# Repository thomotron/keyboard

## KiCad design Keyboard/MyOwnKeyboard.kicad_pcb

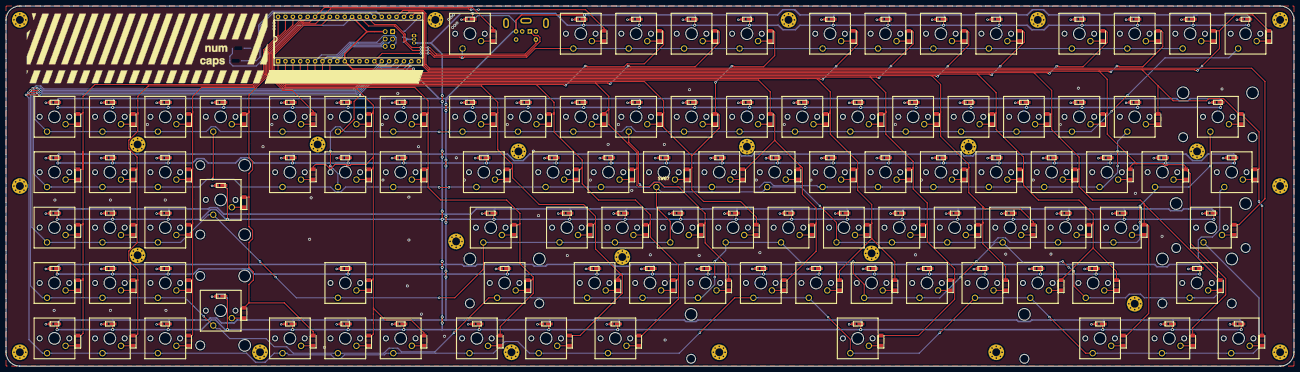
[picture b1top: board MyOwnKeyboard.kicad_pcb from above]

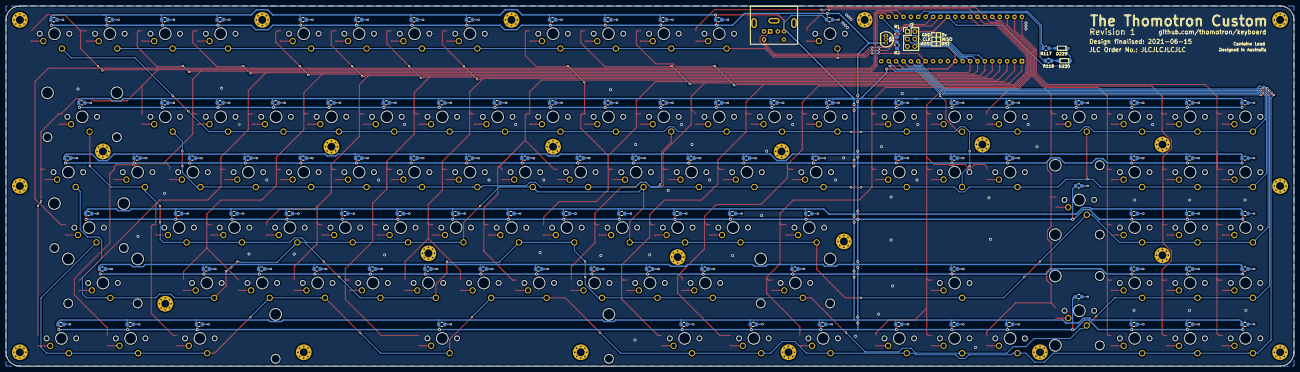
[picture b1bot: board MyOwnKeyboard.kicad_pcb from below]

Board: 2 copper layers, 441.8 x 123.5 mm, 438 parts (110 on the bottom side), 239 nets.

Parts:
D5, D6, D7, D8, D9, D10, D12, D13, D14, D15, D16, D17, D18, D20, D21, D22, D23, D24, D25, D26, D27, D28, D29, D30, D31, D32, D33, D34, D35, D36, D37, D39, D40, D41, D42, D43, D44, D45, D46, D47, D48, D49, D50, D51, D52, D53, D54, D55, D56, D58, D59, D60, D61, D62, D63, D64, D65, D66, D67, D68, D69, D70, D71, D72, D73, D74, D75, D77, D78, D79, D80, D81, D82, D83, D84, D85, D86, D87, D88, D89, D90, D91, D92, D94, D96, D97, D98, D99, D100, D101, D102, D103, D106, D107, D108, D109, D110, D111, D112, D113, D114: 1N4148; D_MiniMELF
D119, D120, D121, D122, D123, D124, D126, D127, D128, D129, D130, D131, D132, D134, D135, D136, D137, D138, D139, D140, D141, D142, D143, D144, D145, D146, D147, D148, D149, D150, D151, D153, D154, D155, D156, D157, D158, D159, D160, D161, D162, D163, D164, D165, D166, D167, D168, D169, D170, D172, D173, D174, D175, D176, D177, D178, D179, D180, D181, D182, D183, D184, D185, D186, D187, D188, D189, D191, D192, D193, D194, D195, D196, D197, D198, D199, D200, D201, D202, D203, D204, D205, D206, D208, D210, D211, D212, D213, D214, D215, D216, D217, D220, D221, D222, D223, D224, D225, D226, D227, D228: LED; 158301250
D229: NUMLOCK; 158301250_Face_Down
D230: CAPSLOCK; 158301250_Face_Down
J1: Mini-DIN-6; Connector_Mini-DIN_Female_6Pin_2rows
J2: ISP Header; PinHeader_2x03_P2.54mm_Vertical
M1, M2, M3, M4, M5, M6, M7, M8, M9, M10, M11, M12, M13, M14, M15, M16, M17, M18, M19, M20, M21, M22, M23, M24: MountingHole_2.7mm_M2.5_Pad_Via
Q1: 2N7000; TO-92_Inline
R1: 100; R_0805_2012Metric_Pad1.15x1.40mm_HandSolder
R2: 100k; R_0805_2012Metric_Pad1.15x1.40mm_HandSolder
R7, R8, R9, R10, R11, R12, R14, R15, R16, R17, R18, R19, R20, R22, R23, R24, R25, R26, R27, R28, R29, R30, R31, R32, R33, R34, R35, R36, R37, R38, R39, R41, R42, R43, R44, R45, R46, R47, R48, R49, R50, R51, R52, R53, R54, R55, R56, R57, R58, R60, R61, R62, R63, R64, R65, R66, R67, R68, R69, R70, R71, R72, R73, R74, R75, R76, R77, R79, R80, R81, R82, R83, R84, R85, R86, R87, R88, R89, R90, R91, R92, R93, R94, R96, R98, R99, R100, R101, R102, R103, R104, R105, R108, R109, R110, R111, R112, R113, R114, R115, R116, R117, R118: 2.26k; R_0805_2012Metric_Pad1.15x1.40mm_HandSolder
SW5, SW6, SW7, SW8, SW9, SW10, SW12, SW13, SW14, SW15, SW16, SW17, SW18, SW20, SW21, SW22, SW23, SW24, SW25, SW26, SW27, SW28, SW29, SW30, SW31, SW32, SW33, SW34, SW35, SW36, SW37, SW39, SW40, SW41, SW42, SW43, SW44, SW46, SW47, SW48, SW49, SW50, SW51, SW52, SW53, SW54, SW55, SW56, SW58, SW59, SW60, SW62, SW64, SW65, SW66, SW67, SW68, SW69, SW70, SW71, SW72, SW73, SW74, SW77, SW78, SW79, SW81, SW83, SW84, SW85, SW86, SW87, SW88, SW89, SW90, SW91, SW96, SW97, SW98, SW99, SW100, SW106, SW107, SW109, SW110: SW_SPST; SW_Cherry_MX_1.00u_PCB
SW45, SW94: SW_SPST; SW_Cherry_MX_1.50u_PCB
SW61, SW80: SW_SPST; SW_Cherry_MX_2.00u_Vertical_PCB
SW63: SW_SPST; SW_Cherry_MX_1.75u_PCB
SW75: SW_SPST; SW_Cherry_MX_2.00u_PCB
SW82, SW114: SW_SPST; SW_Cherry_MX_2.25u_PCB
SW92: SW_SPST; SW_Cherry_MX_2.75u_PCB
SW101, SW102, SW103, SW111, SW112, SW113: SW_SPST; SW_Cherry_MX_1.25u_PCB
SW108: SW_SPST; SW_Cherry_MX_7.00u_PCB
U1: ATmega8535-16PU; DIP-40_W15.24mm_Socket

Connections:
1: SW5.1, SW6.1, SW7.1, SW8.1, SW9.1, SW10.1, SW12.1, SW13.1, SW14.1, SW15.1, SW16.1, SW17.1, SW18.1, U1.14
2: SW20.1, SW21.1, SW22.1, SW23.1, SW24.1, SW25.1, SW26.1, SW27.1, SW28.1, SW29.1, SW30.1, SW31.1, SW32.1, SW33.1, SW34.1, SW35.1, SW36.1, SW37.1, U1.15
3: SW39.1, SW40.1, SW41.1, SW42.1, SW43.1, SW44.1, SW45.1, SW46.1, SW47.1, SW48.1, SW49.1, SW50.1, SW51.1, SW52.1, SW53.1, SW54.1, SW55.1, SW56.1, U1.16
4: SW58.1, SW59.1, SW60.1, SW61.1, SW62.1, SW63.1, SW64.1, SW65.1, SW66.1, SW67.1, SW68.1, SW69.1, SW70.1, SW71.1, SW72.1, SW73.1, SW74.1, SW75.1, U1.17
5: SW77.1, SW78.1, SW79.1, SW80.1, SW81.1, SW82.1, SW83.1, SW84.1, SW85.1, SW86.1, SW87.1, SW88.1, SW89.1, SW90.1, SW91.1, SW92.1, SW94.1, U1.18
5v: D229.2, D230.2, J1.4, J2.2, R7.1, R8.1, R9.1, R10.1, R11.1, R12.1, R14.1, R15.1, R16.1, R17.1, R18.1, R19.1, R20.1, R22.1, R23.1, R24.1, R25.1, R26.1, R27.1, R28.1, R29.1, R30.1, R31.1, R32.1, R33.1, R34.1, R35.1, R36.1, R37.1, R38.1, R39.1, R41.1, R42.1, R43.1, R44.1, R45.1, R46.1, R47.1, R48.1, R49.1, R50.1, R51.1, R52.1, R53.1, R54.1, R55.1, R56.1, R57.1, R58.1, R60.1, R61.1, R62.1, R63.1, R64.1, R65.1, R66.1, R67.1, R68.1, R69.1, R70.1, R71.1, R72.1, R73.1, R74.1, R75.1, R76.1, R77.1, R79.1, R80.1, R81.1, R82.1, R83.1, R84.1, R85.1, R86.1, R87.1, R88.1, R89.1, R90.1, R91.1, R92.1, R93.1, R94.1, R96.1, R98.1, R99.1, R100.1, R101.1, R102.1, R103.1, R104.1, R105.1, R108.1, R109.1, R110.1, R111.1, R112.1, R113.1, R114.1, R115.1, R116.1, U1.10, U1.30
6: SW96.1, SW97.1, SW98.1, SW99.1, SW100.1, SW101.1, SW102.1, SW103.1, SW106.1, SW107.1, SW108.1, SW109.1, SW110.1, SW111.1, SW112.1, SW113.1, SW114.1, U1.19
/Clk: J1.5, U1.28
/Counter2A-PWM: R1.1, U1.21
/Data: J1.1, U1.29
A: D20.2, D39.2, D58.2, D77.2, D96.2, U1.40
B: D21.2, D40.2, D59.2, D78.2, D97.2, U1.39
C: D22.2, D41.2, D60.2, D79.2, D98.2, U1.38
D: D23.2, D42.2, D61.2, D80.2, D99.2, U1.37
E: D5.2, D24.2, D43.2, D62.2, D81.2, D100.2, U1.36
Earth: J1.3, J2.1, Q1.1, R2.2, U1.11, U1.25, U1.31
F: D6.2, D25.2, D44.2, D63.2, D82.2, D101.2, U1.35
G: D7.2, D26.2, D45.2, D64.2, D83.2, D102.2, U1.34
H: D8.2, D27.2, D46.2, D65.2, D84.2, D103.2, U1.33
I: D9.2, D28.2, D47.2, D66.2, D85.2, U1.1
J: D10.2, D29.2, D48.2, D67.2, D86.2, U1.2
K: D30.2, D49.2, D68.2, D87.2, D106.2, U1.3
L: D12.2, D31.2, D50.2, D69.2, D88.2, D107.2, U1.4
M: D13.2, D32.2, D51.2, D70.2, D89.2, D108.2, U1.5
MISO: D15.2, D34.2, D53.2, D72.2, D91.2, D110.2, J2.4, U1.7
MOSI: D14.2, D33.2, D52.2, D71.2, D90.2, D109.2, J2.5, U1.6
unnamed: D5.1, SW5.2
unnamed: D6.1, SW6.2
unnamed: D7.1, SW7.2
unnamed: D8.1, SW8.2
unnamed: D9.1, SW9.2
unnamed: D10.1, SW10.2
unnamed: D12.1, SW12.2
unnamed: D13.1, SW13.2
unnamed: D14.1, SW14.2
unnamed: D15.1, SW15.2
unnamed: D16.1, SW16.2
unnamed: D17.1, SW17.2
unnamed: D18.1, SW18.2
unnamed: D20.1, SW20.2
unnamed: D21.1, SW21.2
unnamed: D22.1, SW22.2
unnamed: D23.1, SW23.2
unnamed: D24.1, SW24.2
unnamed: D25.1, SW25.2
unnamed: D26.1, SW26.2
unnamed: D27.1, SW27.2
unnamed: D28.1, SW28.2
unnamed: D29.1, SW29.2
unnamed: D30.1, SW30.2
unnamed: D31.1, SW31.2
unnamed: D32.1, SW32.2
unnamed: D33.1, SW33.2
unnamed: D34.1, SW34.2
unnamed: D35.1, SW35.2
unnamed: D36.1, SW36.2
unnamed: D37.1, SW37.2
unnamed: D39.1, SW39.2
unnamed: D40.1, SW40.2
unnamed: D41.1, SW41.2
unnamed: D42.1, SW42.2
unnamed: D43.1, SW43.2
unnamed: D44.1, SW44.2
unnamed: D45.1, SW45.2
unnamed: D46.1, SW46.2
unnamed: D47.1, SW47.2
unnamed: D48.1, SW48.2
unnamed: D49.1, SW49.2
unnamed: D50.1, SW50.2
unnamed: D51.1, SW51.2
unnamed: D52.1, SW52.2
unnamed: D53.1, SW53.2
unnamed: D54.1, SW54.2
unnamed: D55.1, SW55.2
unnamed: D56.1, SW56.2
unnamed: D58.1, SW58.2
unnamed: D59.1, SW59.2
unnamed: D60.1, SW60.2
unnamed: D61.1, SW61.2
unnamed: D62.1, SW62.2
unnamed: D63.1, SW63.2
unnamed: D64.1, SW64.2
unnamed: D65.1, SW65.2
unnamed: D66.1, SW66.2
unnamed: D67.1, SW67.2
unnamed: D68.1, SW68.2
unnamed: D69.1, SW69.2
unnamed: D70.1, SW70.2
unnamed: D71.1, SW71.2
unnamed: D72.1, SW72.2
unnamed: D73.1, SW73.2
unnamed: D74.1, SW74.2
unnamed: D75.1, SW75.2
unnamed: D77.1, SW77.2
unnamed: D78.1, SW78.2
unnamed: D79.1, SW79.2
unnamed: D80.1, SW80.2
unnamed: D81.1, SW81.2
unnamed: D82.1, SW82.2
unnamed: D83.1, SW83.2
unnamed: D84.1, SW84.2
unnamed: D85.1, SW85.2
unnamed: D86.1, SW86.2
unnamed: D87.1, SW87.2
unnamed: D88.1, SW88.2
unnamed: D89.1, SW89.2
unnamed: D90.1, SW90.2
unnamed: D91.1, SW91.2
unnamed: D92.1, SW92.2
unnamed: D94.1, SW94.2
unnamed: D96.1, SW96.2
unnamed: D97.1, SW97.2
unnamed: D98.1, SW98.2
unnamed: D99.1, SW99.2
unnamed: D100.1, SW100.2
unnamed: D101.1, SW101.2
unnamed: D102.1, SW102.2
unnamed: D103.1, SW103.2
unnamed: D106.1, SW106.2
unnamed: D107.1, SW107.2
unnamed: D108.1, SW108.2
unnamed: D109.1, SW109.2
unnamed: D110.1, SW110.2
unnamed: D111.1, SW111.2
unnamed: D112.1, SW112.2
unnamed: D113.1, SW113.2
unnamed: D114.1, SW114.2
unnamed: D119.1, D120.1, D121.1, D122.1, D123.1, D124.1, D126.1, D127.1, D128.1, D129.1, D130.1, D131.1, D132.1, D134.1, D135.1, D136.1, D137.1, D138.1, D139.1, D140.1, D141.1, D142.1, D143.1, D144.1, D145.1, D146.1, D147.1, D148.1, D149.1, D150.1, D151.1, D153.1, D154.1, D155.1, D156.1, D157.1, D158.1, D159.1, D160.1, D161.1, D162.1, D163.1, D164.1, D165.1, D166.1, D167.1, D168.1, D169.1, D170.1, D172.1, D173.1, D174.1, D175.1, D176.1, D177.1, D178.1, D179.1, D180.1, D181.1, D182.1, D183.1, D184.1, D185.1, D186.1, D187.1, D188.1, D189.1, D191.1, D192.1, D193.1, D194.1, D195.1, D196.1, D197.1, D198.1, D199.1, D200.1, D201.1, D202.1, D203.1, D204.1, D205.1, D206.1, D208.1, D210.1, D211.1, D212.1, D213.1, D214.1, D215.1, D216.1, D217.1, D220.1, D221.1, D222.1, D223.1, D224.1, D225.1, D226.1, D227.1, D228.1, Q1.3
unnamed: D119.2, R7.2
unnamed: D120.2, R8.2
unnamed: D121.2, R9.2
unnamed: D122.2, R10.2
unnamed: D123.2, R11.2
unnamed: D124.2, R12.2
unnamed: D126.2, R14.2
unnamed: D127.2, R15.2
unnamed: D128.2, R16.2
unnamed: D129.2, R17.2
unnamed: D130.2, R18.2
unnamed: D131.2, R19.2
unnamed: D132.2, R20.2
unnamed: D134.2, R22.2
unnamed: D135.2, R23.2
unnamed: D136.2, R24.2
unnamed: D137.2, R25.2
unnamed: D138.2, R26.2
unnamed: D139.2, R27.2
unnamed: D140.2, R28.2
unnamed: D141.2, R29.2
unnamed: D142.2, R30.2
unnamed: D143.2, R31.2
unnamed: D144.2, R32.2
unnamed: D145.2, R33.2
unnamed: D146.2, R34.2
unnamed: D147.2, R35.2
unnamed: D148.2, R36.2
unnamed: D149.2, R37.2
unnamed: D150.2, R38.2
unnamed: D151.2, R39.2
unnamed: D153.2, R41.2
unnamed: D154.2, R42.2
unnamed: D155.2, R43.2
unnamed: D156.2, R44.2
unnamed: D157.2, R45.2
unnamed: D158.2, R46.2
unnamed: D159.2, R47.2
unnamed: D160.2, R48.2
unnamed: D161.2, R49.2
unnamed: D162.2, R50.2
unnamed: D163.2, R51.2
unnamed: D164.2, R52.2
unnamed: D165.2, R53.2
unnamed: D166.2, R54.2
unnamed: D167.2, R55.2
unnamed: D168.2, R56.2
unnamed: D169.2, R57.2
unnamed: D170.2, R58.2
unnamed: D172.2, R60.2
unnamed: D173.2, R61.2
unnamed: D174.2, R62.2
unnamed: D175.2, R63.2
unnamed: D176.2, R64.2
unnamed: D177.2, R65.2
unnamed: D178.2, R66.2
unnamed: D179.2, R67.2
unnamed: D180.2, R68.2
unnamed: D181.2, R69.2
unnamed: D182.2, R70.2
unnamed: D183.2, R71.2
unnamed: D184.2, R72.2
unnamed: D185.2, R73.2
unnamed: D186.2, R74.2
unnamed: D187.2, R75.2
unnamed: D188.2, R76.2
unnamed: D189.2, R77.2
unnamed: D191.2, R79.2
unnamed: D192.2, R80.2
unnamed: D193.2, R81.2
unnamed: D194.2, R82.2
unnamed: D195.2, R83.2
unnamed: D196.2, R84.2
unnamed: D197.2, R85.2
unnamed: D198.2, R86.2
unnamed: D199.2, R87.2
unnamed: D200.2, R88.2
unnamed: D201.2, R89.2
unnamed: D202.2, R90.2
unnamed: D203.2, R91.2
unnamed: D204.2, R92.2
unnamed: D205.2, R93.2
unnamed: D206.2, R94.2
unnamed: D208.2, R96.2
unnamed: D210.2, R98.2
unnamed: D211.2, R99.2
unnamed: D212.2, R100.2
unnamed: D213.2, R101.2
unnamed: D214.2, R102.2
unnamed: D215.2, R103.2
unnamed: D216.2, R104.2
unnamed: D217.2, R105.2
unnamed: D220.2, R108.2
unnamed: D221.2, R109.2
unnamed: D222.2, R110.2
unnamed: D223.2, R111.2
unnamed: D224.2, R112.2
unnamed: D225.2, R113.2
unnamed: D226.2, R114.2
unnamed: D227.2, R115.2
unnamed: D228.2, R116.2
unnamed: D229.1, R117.2
unnamed: D230.1, R118.2
unnamed: Q1.2, R1.2, R2.1
unnamed: R117.1, U1.26
unnamed: R118.1, U1.27
P: D16.2, D35.2, D54.2, D73.2, D92.2, D111.2, J2.3, U1.8
Q: D17.2, D36.2, D55.2, D74.2, D112.2, U1.22
R: D18.2, D37.2, D56.2, D75.2, D94.2, D113.2, U1.23
RESET: J2.6, U1.9
S: D114.2, U1.24

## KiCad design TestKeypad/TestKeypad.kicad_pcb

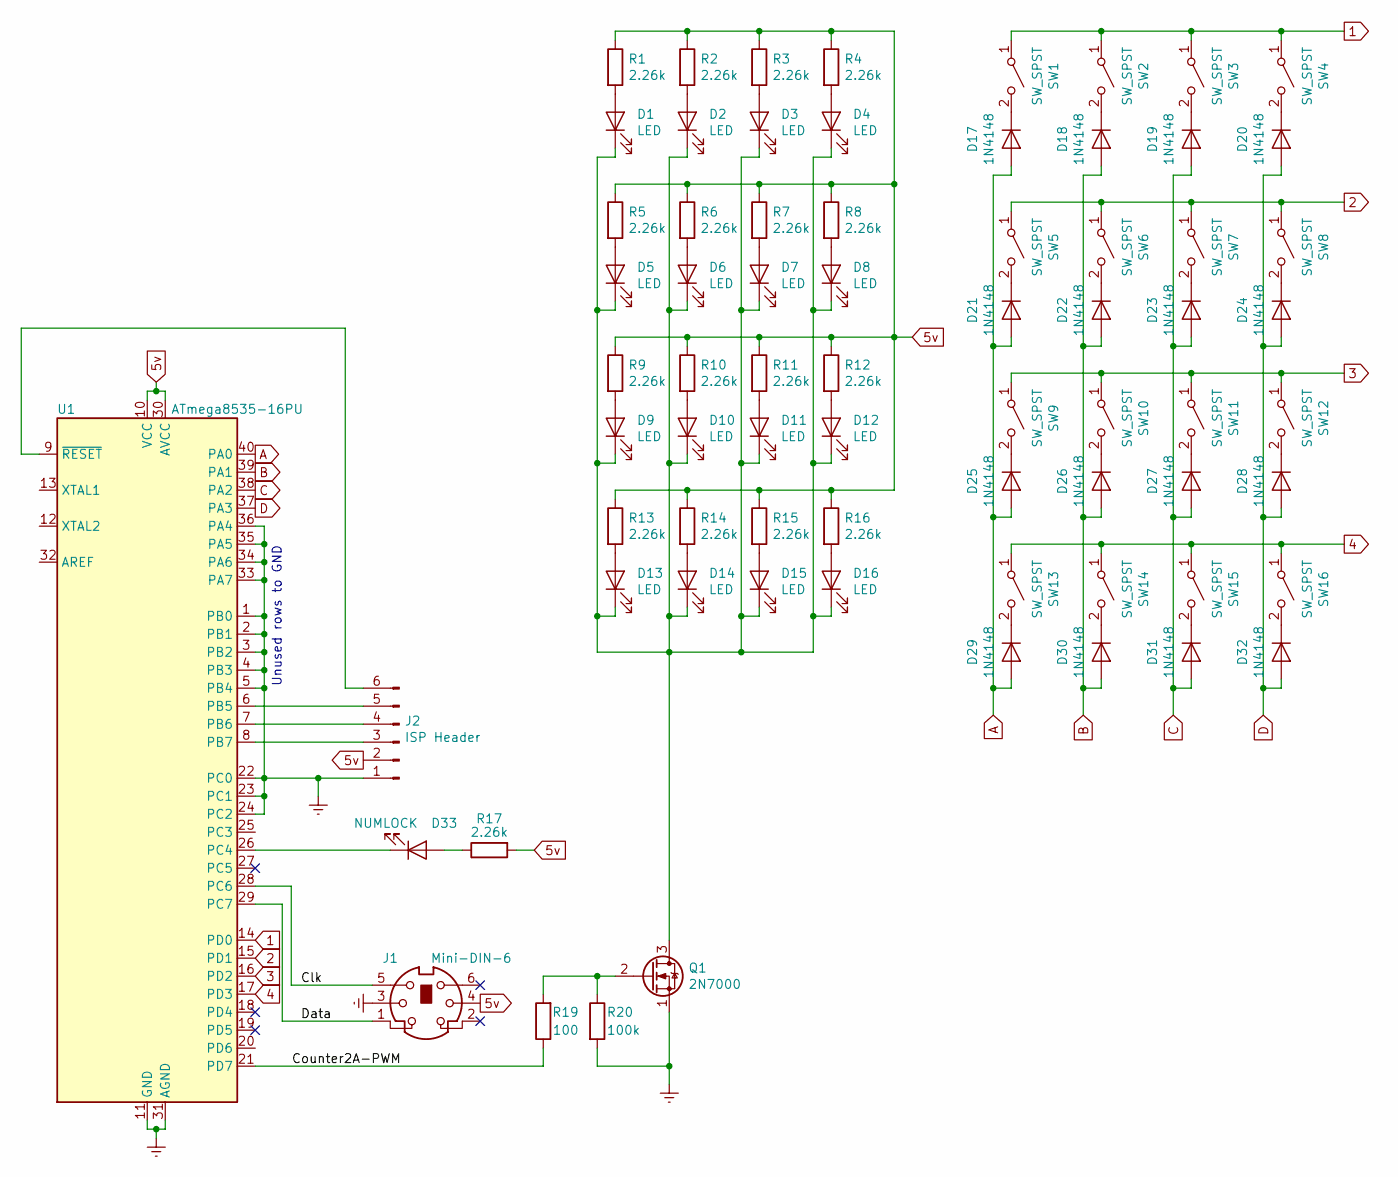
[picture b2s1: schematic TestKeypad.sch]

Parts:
D1, D2, D3, D4, D5, D6, D7, D8, D9, D10, D11, D12, D13, D14, D15, D16: LED; 158301250
D17, D18, D19, D20, D21, D22, D23, D24, D25, D26, D27, D28, D29, D30, D31, D32: 1N4148; D_MiniMELF
D33: NUMLOCK; 158301250
J1: Mini-DIN-6; Connector_Mini-DIN_Female_6Pin_2rows
J2: ISP Header; PinHeader_2x03_P2.54mm_Vertical
Q1: 2N7000; TO-92_Inline
R1, R2, R3, R4, R5, R6, R7, R8, R9, R10, R11, R12, R13, R14, R15, R16, R17: 2.26k; R_0805_2012Metric_Pad1.15x1.40mm_HandSolder
R19: 100; R_0805_2012Metric_Pad1.15x1.40mm_HandSolder
R20: 100k; R_0805_2012Metric_Pad1.15x1.40mm_HandSolder
SW1, SW2, SW3, SW4, SW5, SW6, SW7, SW8, SW9, SW10, SW11, SW12, SW13, SW14, SW15, SW16: SW_SPST; SW_Cherry_MX_1.00u_PCB
U1: ATmega8535-16PU; DIP-40_W15.24mm_Socket

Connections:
1: SW1.1 (A), SW2.1 (A), SW3.1 (A), SW4.1 (A), U1.14 (PD0)
2: SW5.1 (A), SW6.1 (A), SW7.1 (A), SW8.1 (A), U1.15 (PD1)
3: SW9.1 (A), SW10.1 (A), SW11.1 (A), SW12.1 (A), U1.16 (PD2)
4: SW13.1 (A), SW14.1 (A), SW15.1 (A), SW16.1 (A), U1.17 (PD3)
5v: J1.4, J2.2, R1.1, R2.1, R3.1, R4.1, R5.1, R6.1, R7.1, R8.1, R9.1, R10.1, R11.1, R12.1, R13.1, R14.1, R15.1, R16.1, R17.2, U1.10 (VCC), U1.30 (AVCC)
/Clk: J1.5, U1.28 (PC6)
/Counter2A-PWM: R19.1, U1.21 (PD7)
/Data: J1.1, U1.29 (PC7)
A: D17.2 (A), D21.2 (A), D25.2 (A), D29.2 (A), U1.40 (PA0)
B: D18.2 (A), D22.2 (A), D26.2 (A), D30.2 (A), U1.39 (PA1)
C: D19.2 (A), D23.2 (A), D27.2 (A), D31.2 (A), U1.38 (PA2)
D: D20.2 (A), D24.2 (A), D28.2 (A), D32.2 (A), U1.37 (PA3)
Earth: J1.3, J2.1, Q1.1 (S), R20.2, U1.1 (PB0), U1.2 (PB1), U1.3 (PB2), U1.4 (PB3), U1.5 (PB4), U1.11 (GND), U1.22 (PC0), U1.23 (PC1), U1.24 (PC2), U1.31 (AGND), U1.33 (PA7), U1.34 (PA6), U1.35 (PA5), U1.36 (PA4)
unnamed: D1.1 (K), D2.1 (K), D3.1 (K), D4.1 (K), D5.1 (K), D6.1 (K), D7.1 (K), D8.1 (K), D9.1 (K), D10.1 (K), D11.1 (K), D12.1 (K), D13.1 (K), D14.1 (K), D15.1 (K), D16.1 (K), Q1.3 (D)
unnamed: D1.2 (A), R1.2
unnamed: D2.2 (A), R2.2
unnamed: D3.2 (A), R3.2
unnamed: D4.2 (A), R4.2
unnamed: D5.2 (A), R5.2
unnamed: D6.2 (A), R6.2
unnamed: D7.2 (A), R7.2
unnamed: D8.2 (A), R8.2
unnamed: D9.2 (A), R9.2
unnamed: D10.2 (A), R10.2
unnamed: D11.2 (A), R11.2
unnamed: D12.2 (A), R12.2
unnamed: D13.2 (A), R13.2
unnamed: D14.2 (A), R14.2
unnamed: D15.2 (A), R15.2
unnamed: D16.2 (A), R16.2
unnamed: D17.1 (K), SW1.2 (B)
unnamed: D18.1 (K), SW2.2 (B)
unnamed: D19.1 (K), SW3.2 (B)
unnamed: D20.1 (K), SW4.2 (B)
unnamed: D21.1 (K), SW5.2 (B)
unnamed: D22.1 (K), SW6.2 (B)
unnamed: D23.1 (K), SW7.2 (B)
unnamed: D24.1 (K), SW8.2 (B)
unnamed: D25.1 (K), SW9.2 (B)
unnamed: D26.1 (K), SW10.2 (B)
unnamed: D27.1 (K), SW11.2 (B)
unnamed: D28.1 (K), SW12.2 (B)
unnamed: D29.1 (K), SW13.2 (B)
unnamed: D30.1 (K), SW14.2 (B)
unnamed: D31.1 (K), SW15.2 (B)
unnamed: D32.1 (K), SW16.2 (B)
unnamed: D33.1 (K), U1.26 (PC4)
unnamed: D33.2 (A), R17.1
unnamed: J2.3, U1.8 (PB7)
unnamed: J2.4, U1.7 (PB6)
unnamed: J2.5, U1.6 (PB5)
unnamed: J2.6, U1.9 (~RESET)
unnamed: Q1.2 (G), R19.2, R20.1

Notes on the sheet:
Unused rows to GND

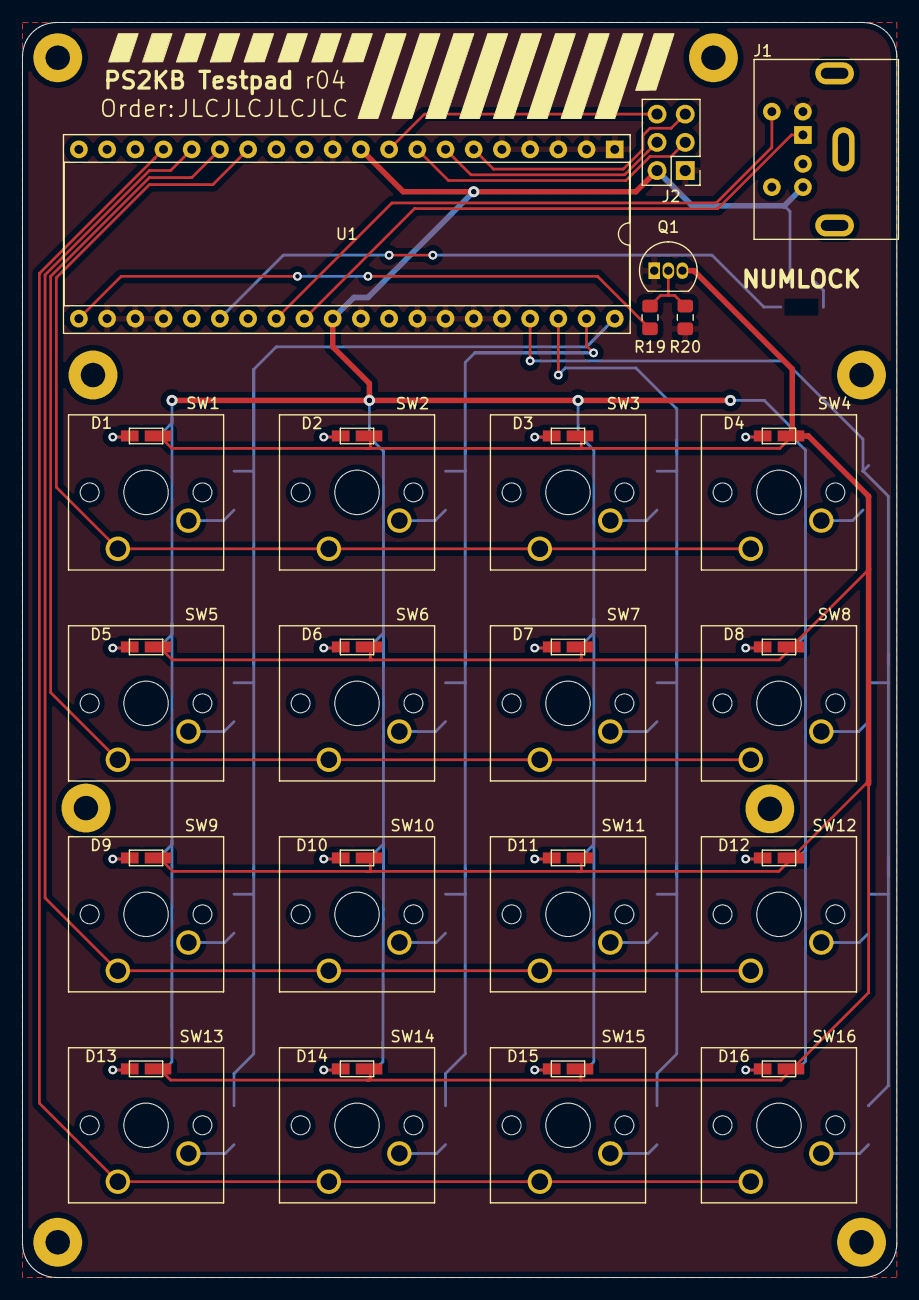
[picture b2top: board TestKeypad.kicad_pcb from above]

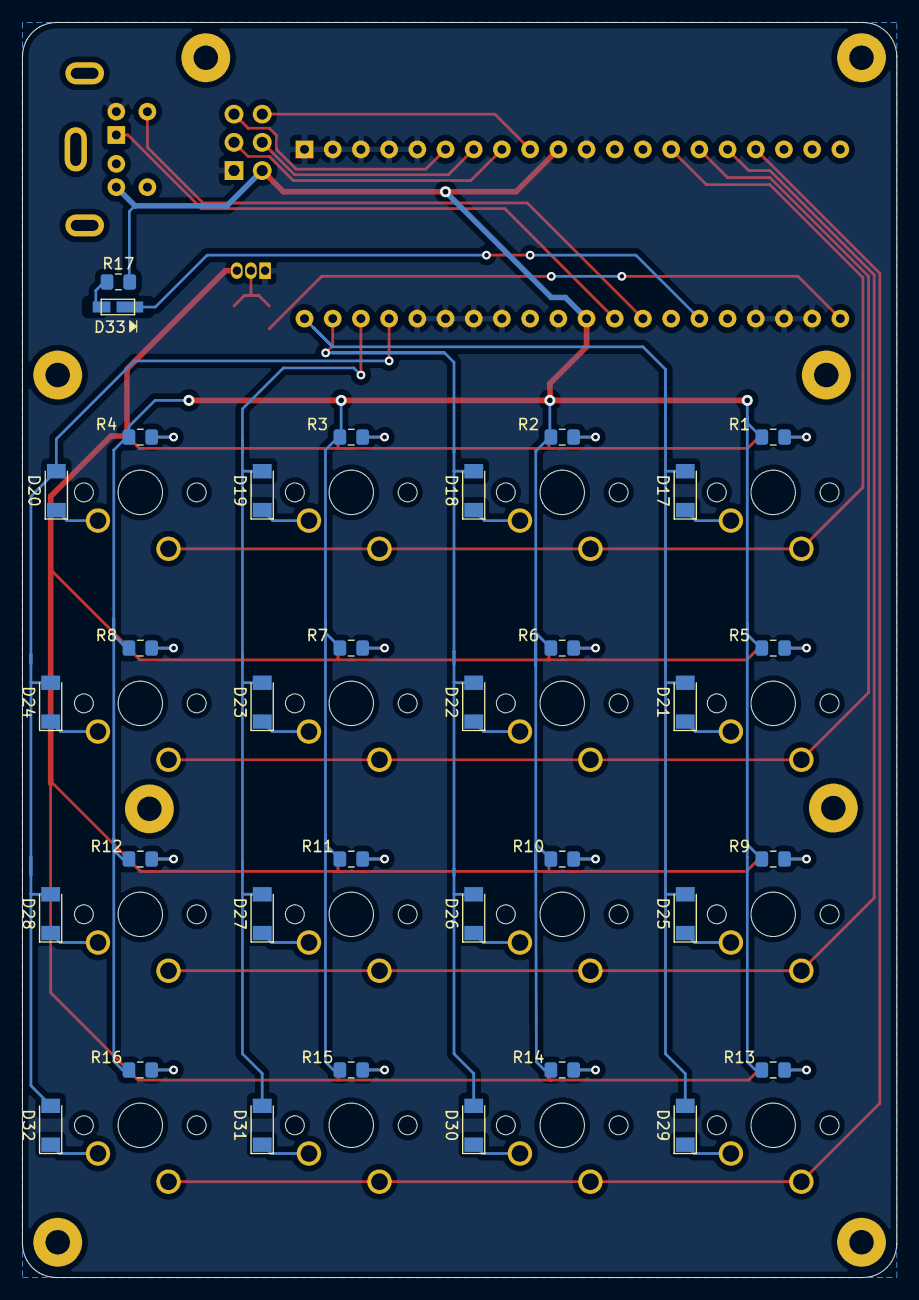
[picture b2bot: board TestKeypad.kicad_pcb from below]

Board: 2 copper layers, 78.7 x 113.0 mm, 72 parts (34 on the bottom side), 53 nets.

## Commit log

2020-05-01 Initial commit 🎉
2020-05-01 Assigned switches Romer-G footprint
2020-05-01 Migrate to the ATMega164
    Why use IO expanders when you can just get more pins. It still turns out ~$3 cheaper.
2020-05-01 Add LED and assign footprints
2020-05-02 Add per-key LEDs, basic PCB layout
2020-05-03 Add NUM/CAPSLOCK indicators, finalise components
2020-05-03 Removed crystal, finalised design
2020-05-03 Update resistor values to squeeze out some of that sweet, sweet current
2020-05-05 Extract libraries and move project down one level
2020-05-10 Add test keypad
    diff --git a/TestKeypad/TestKeypad-cache.lib b/TestKeypad/TestKeypad-cache.lib
    new file mode 100644
    index 0000000..1c2d1c4
    --- /dev/null
    +++ b/TestKeypad/TestKeypad-cache.lib
    @@ -0,0 +1,198 @@
2020-05-10 Finalise test keypad r01 and silkscreen
2020-05-22 Initial working concept
2020-05-23 Proper working implementation with PS2dev
2020-05-23 Don't bother writing extended fuse bits
2020-05-29 Add keyboard map and handler
2020-05-29 Implement test keypad
2020-05-30 Add script to generate keymaps
    It's still hard-coded, but it's easier than translating each key into its respective scan codes.
2020-05-30 Tidy up matrix code and add sample keymap
2020-05-30 Ignore python artifacts
2020-06-01 Fix the keypad issue
    I presume it's nothing to do with the extracted functions and more to do with manually resetting each pin before resampling.
2020-06-01 Neaten up the keypad reading logic
    The whole keypad is scanned before sending anything to the host for completeness.
    It was the row reset that fixed the issue.
2020-06-01 Add missing docs
2020-06-01 Reset keyboard matrix rows
    Avoids the complications had in 78cab8a
2020-06-01 Refactor readMatrix()
    As with readKeypad, readMatrix now scans the entire matrix before acting on anything.
2020-06-02 Move KP1 pin to PORTD5
2020-06-02 Add PWMed backlight controlled by * and # keys
2020-06-02 Remove CLK and DATA LEDs
    These are actually a part of the lines themselves now, so no need to waste cycles updating them anymore.
    Not that they were particularly reliable anyway.
2020-06-02 Toggle PWM when setting backlight to zero
    The backlight should be *all the way* off instead of just kinda off when it's set to off.
2020-06-03 Actually set the fuses properly
    Turns out avrdude's `-u` disables safemode and allows writing the fuses. A true case of RTFM right here.
2020-06-03 Properly enable and disable backlight clock source
2020-06-03 Fix issue where backlight will underflow and turn on
    It'd be handy if OCR2 were treated as an int by the inference of `increment`
2020-06-04 Reword TCCR2 comments to be more useful
    I don't care what 'WGM' is, I want to know what that line of code does.
2020-06-04 Remove button definition
2020-06-06 Add timed interrupt to check for host comms
    It's much easier (and more reliable) to periodically break execution and check if the host wants to talk.
    This isn't a major problem when polling the matrix, but it is when we are transmitting, so interrupts are disabled when sending make/break codes.
2020-06-06 Correctly reset PORTD when polling matrix
2020-06-06 Sample CLK *and* DATA when checking for PS/2 RTS
    The CLK line is only held low for 100μs which is incredibly hard to catch. I tried solving this with an interrupt, but for some reason my system drops CLK a few times a second for no apparent reason,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
    After probing DATA for a bit, it seems that it gets held low significantly longer and is generally more reliable than checking CLK (this issue was also expressed in Harvie/ps2dev#8).
2020-06-06 No, that's not how that works
    I was just cooked and had gotten confused with the DDR bits (0: in, 1: out).
    0 == 0, 1 == 1.
2020-06-06 Store backlight state in EEPROM
2020-06-06 Store LED states explicitly
2020-06-06 Add make target to set default EEPROM content
2020-06-06 Break backlight brightness functions down
    There's no need to take an arbitrary signed integer and try process that when we already rely on a definition to change the value.
    Due to an issue with the output compare module, only the output pin is disabled when disabling the backlight. This is because, if timed just right, the pin would remain toggled high when the timer is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
2020-06-06 Use triple slash for function/variable documentation
2020-06-07 Inline some functions for efficiency
    TIL that function calls are rather expensive cycle-wise
2020-06-07 Refactor handleKeypress with switches
    Making lots of exceptions in an if-else will look ugly later on
2020-06-07 Fix macro keys sending break codes
2020-06-07 Fix more weird inversion cookery
2020-06-07 Rework to match keyboard matrix schematic
    All debug and keypad logic has been removed to try ready this for testing in a production environment.
2020-06-08 Fix status LEDs
    Seems the compiler dislikes inline ternary when combined with defines
2020-07-24 Revise test keypad to r02
    Updated components to match the actual board and revised PCB layout
2020-08-01 Revise test keypad to r03
    Tweaked just before making a production run
    Added screw holes
    Added an ISP header
    Added pulldown resistor array to switch input lines
    Also remapped an incorrectly-placed "GND" label to the actual ground net (which slipped through into the production run)
2020-08-01 Update keyboard to match changes to keypad
2020-08-01 Change PS/2 socket and transistor references
2020-08-01 Rename matrix driver pins
    Nets are case-insensitive, so the driver pins are now 1-6 instead of a-f
2020-08-01 Update keyboard PCB template to match schematic
2020-08-01 Update diode and switch footprints
2020-08-03 Add custom cherry switch footprints
    Derived from those in the default libraries, but with the centre of the footprint actually in the centre of the footprint, not on pin 1.
2020-08-04 Add Mini-DIN model
2020-09-19 Remove unnecessary variables
2020-11-11 Add function key
2020-11-11 Add toggle for sending PS2 make/break codes
2020-11-11 Use pullup-sink method instead of pulldown
    Was having trouble with the pulldown resistors being finnicky.
    Instead of dealing with that, now we are reading the matrix from each column, using PORTD as a togglable sink (instead of being set high) for each row, and using ports A-C configured with pullups to 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
    This is considerably more reliable than the previous solution and requires minimal hardware change.
2020-11-12 Tweak firmware for the test keypad (r02)
2020-11-12 Parameterise matrix size and reading logic
2020-11-12 Make matrix schematic compliant with pullup-sink method
    See 64d5791
2020-11-12 Reverse diode orientation and reduce pad size
2020-11-12 Update keypad also
2020-11-12 Revise test keypad to r04
    Flipped numlock LED to the back of the board, using it as a diffuser
    Added design to blank area at the top
    Rounded off the corners
2020-11-21 Add component metadata incl. KiCost part details
2020-11-22 Add debounce logic
    Key changes are ignored for one cycle to allow them to settle.
2020-11-22 Tweak firmware for the test keypad (r04)
2020-12-02 Add second layer
2020-12-05 Polish up template
2020-12-07 Support different backlight levels per layer
    Backlight brightness levels now saved per-layer
    Active layer is saved to and loaded from EEPROM at boot
    Added EEPROM address macros for future expansion
2020-12-12 Finalise routing
2020-12-12 Initial layout
2020-12-13 Finalise board for production
    Removed most silkscreen footprint references for switches, diodes, and resistors
    Added a legend for the ISP header
    Filled in as much ground as possible
2020-12-14 Add FnLock
    When pressed, FnLock will toggle Fn. The normal Fn key is inverted while FnLock is toggled on.
2020-12-24 Allow sending arbitrary data from host to device
    Adds a new scancode that can be sent from the host: 0xCX
    The upper part of the byte is always 0xC which distinguishes it from other codes, and the lower part of the byte represents the number of bytes to follow which are part of the same command. (i.e. 0xC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
    This allows up to 16 bytes to be sent (including the initial scancode) in one go, opening up avenues for more dynamic reprogramming of the key layout, backlight, etc.
2021-01-30 Add MX switch, Mini-DIN 6 socket, and LED 3D models
2021-01-30 Add design
2021-01-30 Update footprints from library
2021-01-31 Add .step and .wrl symlinks for each key style
2021-04-14 Add Inventor enclosure prototype
2021-06-15 Finalise revision 1 design
2021-06-15 Add enclosure work
2021-11-23 Split keymap and key into their own headers
2021-11-23 Clarify what either half of the keypress if block is
2021-11-30 Toggle fnLock
2021-11-30 Add key debouncing delay
    Based off of Timer1 which ticks at a rate of once per microsecond.
    All keys must now remain in the same state for at least KEY_BOUNCE_DELAY
    microseconds before they will be handled as a keypress.
2021-11-30 Make layers a bit more dynamic
    Up to 256 layers can be added now, just need to make sure that the
    LAYERS definition is set accordingly.
2021-11-30 Move active layer in EEPROM to first address
    Layer count can freely change without mucking up the set layer
2021-12-01 Consense bool fields to conserve flash
2021-12-07 Add support for raw data over PS/2
    Host can send a command (0xBB in this case) to switch the device to raw
    byte mode. This will cause `keyboard_handle` to pass back a raw byte
    sent by the host instead of interpreting it as a command.
    True commands can still be sent by using an escape code (0xAA in this
    case) which will trigger normal interpretation for the following byte.
2021-12-07 Handle raw data when processing host commands
2021-12-07 Add reset function
    Hacky, sure, but it beats hard wiring the reset pin
2021-12-08 Don't ignore on fn because we want to use fn
2021-12-08 Slightly optimise ps2dev
    Removed unused keypress functions since they took up an extra ~300 bytes
    of flash despite being unused.
    Inlined rudimentary IO functions.
2021-12-16 Add slimmed-down bootloader
    Added bootloader that will wait for a magic number from the host before
    loading in firmware as sequential bytes from PS/2.
    Uses a customised ps2dev instance optimised for size and manages to just
    fit within 1024 bytes of boot space.
2021-12-17 Respond to incoming bytes
2021-12-17 Set bootloader start address to 0x0C00
2022-01-27 Update keymap to match my layout
2022-01-27 Accept direct hex values in layout generator
